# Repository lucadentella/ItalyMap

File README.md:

# ItalyMap

## Description / *Descrizione*
ItalyMap is an electronic project to create a dynamic map of Italy. Thanks to the use of RGB LEDs, one for each Italian region, it is possible to give a visual representation of data relating to these regions.

*ItalyMap è un progetto elettronico per realizzare una mappa dell'Italia dinamica. Grazie all'uso di led RGB, uno per ogni regione italiana, è possibile dare una rappresentazione visuale di dati relativi a tali regioni.*
## Folders / *Cartelle*
 - **eagle**, project in Autodesk Eagle format / *progetto in formato Autodesk Eagle*
 - **gerber**, gerber files ready for manufacturing (JLCPCB service) / *files gerber pronti per la produzione (service JLCPCB)*
 - **sketch**, Arduino programs (esp8266 board) / *programmi Arduino (scheda esp8266)*
 	 - Test_Italian-Flag, displays italian flag / *visualizza la bandiera italiana*
	 - Covid_NewCases-perRegion, displays the new Covid-19 cases / *visualizza i nuovi casi di Covid-19*
	 - Covid_VaccinationRate-perRegion, displays the vaccination rate / *visualizza il numero di vaccinazioni*
## Partlist / *Elenco componenti*
 - [SK6812 MINI-E](https://www.aliexpress.com/item/4000475685852.html) addressable LED
 - 1x03 pinhead
 - Wemos D1 Mini (to run Arduino example)
### Test_Italian-Flag:
 
### Covid_NewCases-perRegion:
 
### Covid_VaccinationRate-perRegion:

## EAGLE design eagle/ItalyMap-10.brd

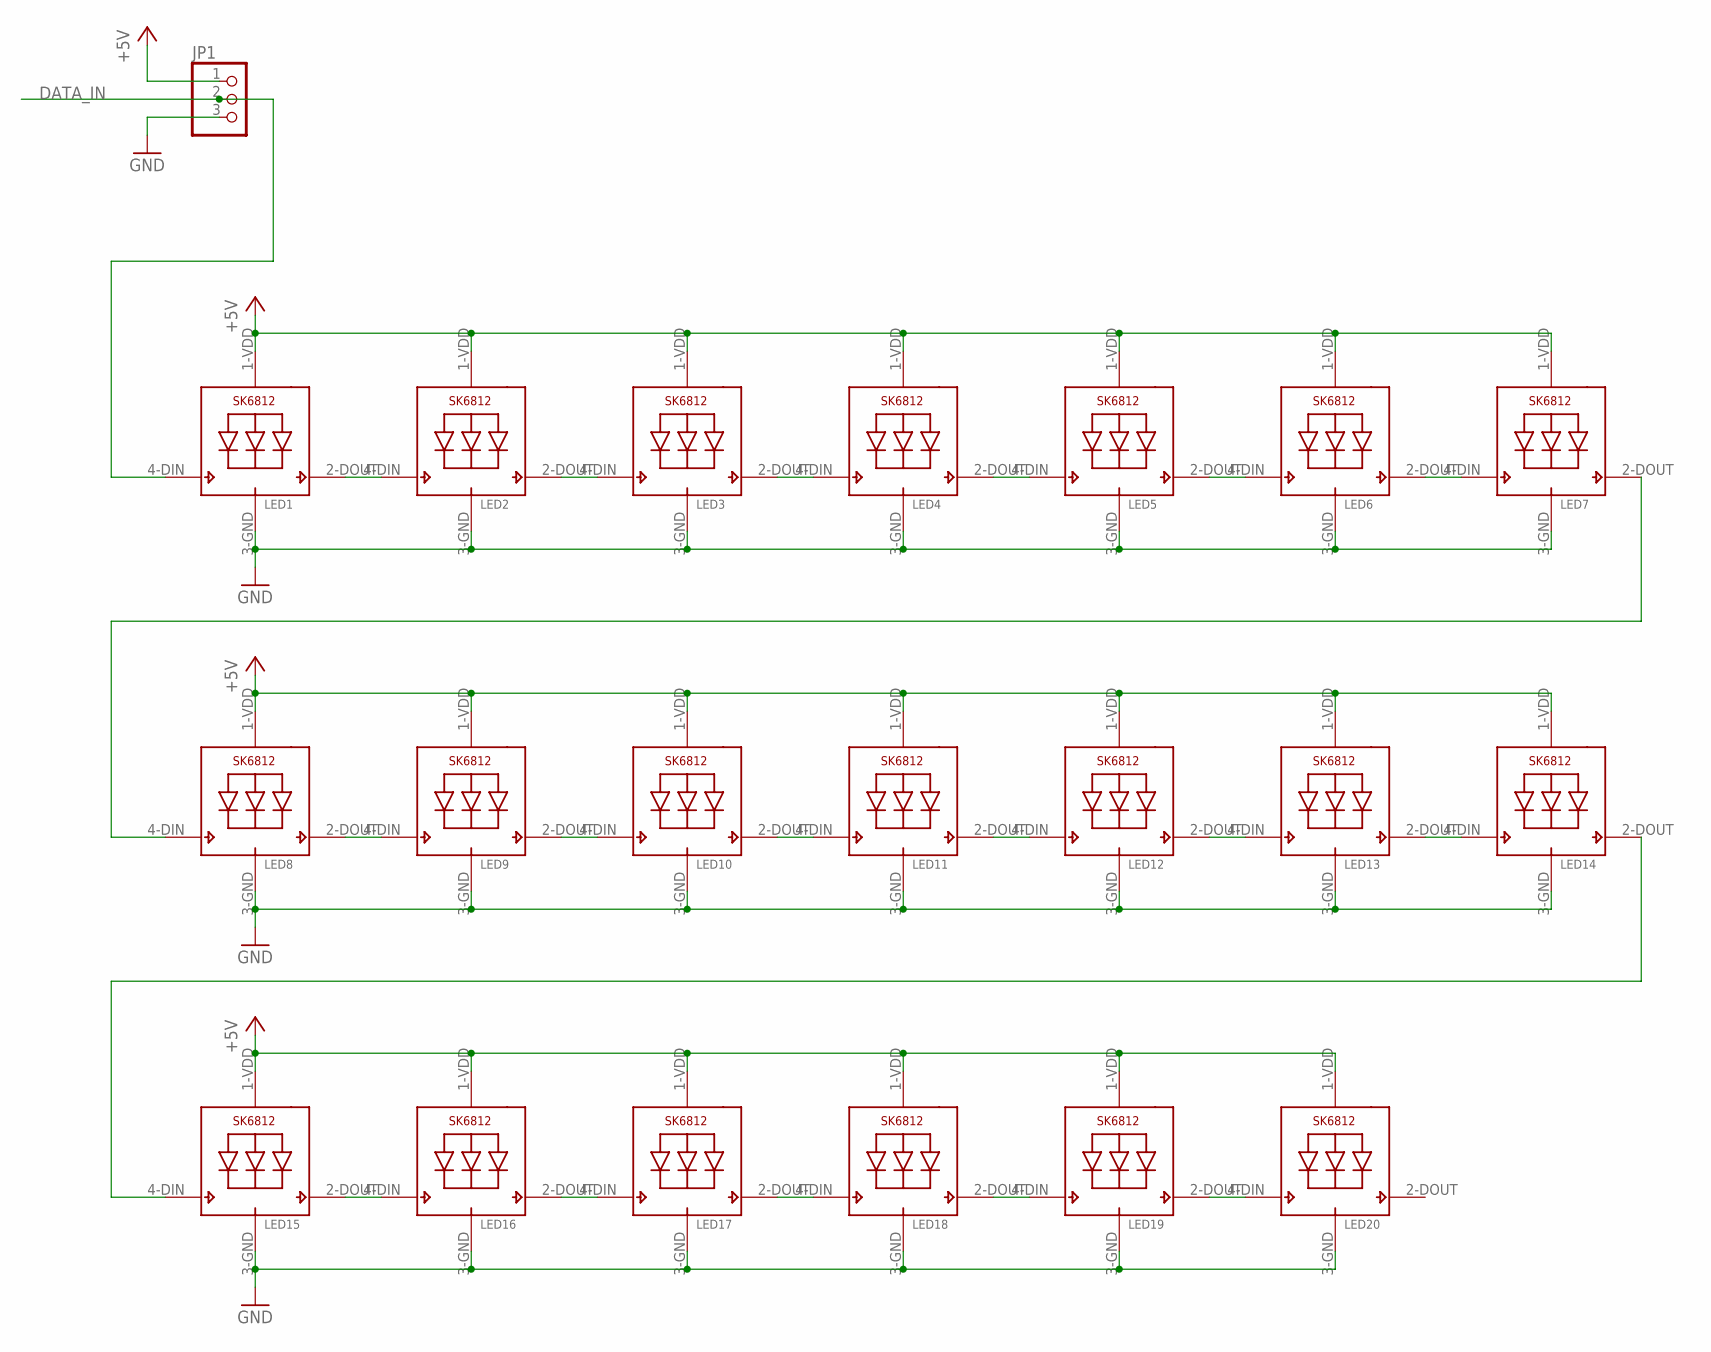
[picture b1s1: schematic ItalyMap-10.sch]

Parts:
JP1: PINHD-1X3; 1X03
LED1, LED2, LED3, LED4, LED5, LED6, LED7, LED8, LED9, LED10, LED11, LED12, LED13, LED14, LED15, LED16, LED17, LED18, LED19, LED20: SK6812; LED3228

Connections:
+5V: JP1.1, LED1.1-VDD (VDD), LED2.1-VDD (VDD), LED3.1-VDD (VDD), LED4.1-VDD (VDD), LED5.1-VDD (VDD), LED6.1-VDD (VDD), LED7.1-VDD (VDD), LED8.1-VDD (VDD), LED9.1-VDD (VDD), LED10.1-VDD (VDD), LED11.1-VDD (VDD), LED12.1-VDD (VDD), LED13.1-VDD (VDD), LED14.1-VDD (VDD), LED15.1-VDD (VDD), LED16.1-VDD (VDD), LED17.1-VDD (VDD), LED18.1-VDD (VDD), LED19.1-VDD (VDD), LED20.1-VDD (VDD)
DATA_IN: JP1.2, LED1.4-DIN (DI)
GND: JP1.3, LED1.3-GND (GND), LED2.3-GND (GND), LED3.3-GND (GND), LED4.3-GND (GND), LED5.3-GND (GND), LED6.3-GND (GND), LED7.3-GND (GND), LED8.3-GND (GND), LED9.3-GND (GND), LED10.3-GND (GND), LED11.3-GND (GND), LED12.3-GND (GND), LED13.3-GND (GND), LED14.3-GND (GND), LED15.3-GND (GND), LED16.3-GND (GND), LED17.3-GND (GND), LED18.3-GND (GND), LED19.3-GND (GND), LED20.3-GND (GND)
unnamed: LED7.2-DOUT (DO), LED8.4-DIN (DI)
unnamed: LED1.2-DOUT (DO), LED2.4-DIN (DI)
unnamed: LED2.2-DOUT (DO), LED3.4-DIN (DI)
unnamed: LED3.2-DOUT (DO), LED4.4-DIN (DI)
unnamed: LED4.2-DOUT (DO), LED5.4-DIN (DI)
unnamed: LED5.2-DOUT (DO), LED6.4-DIN (DI)
unnamed: LED6.2-DOUT (DO), LED7.4-DIN (DI)
unnamed: LED8.2-DOUT (DO), LED9.4-DIN (DI)
unnamed: LED9.2-DOUT (DO), LED10.4-DIN (DI)
unnamed: LED10.2-DOUT (DO), LED11.4-DIN (DI)
unnamed: LED11.2-DOUT (DO), LED12.4-DIN (DI)
unnamed: LED12.2-DOUT (DO), LED13.4-DIN (DI)
unnamed: LED13.2-DOUT (DO), LED14.4-DIN (DI)
unnamed: LED14.2-DOUT (DO), LED15.4-DIN (DI)
unnamed: LED15.2-DOUT (DO), LED16.4-DIN (DI)
unnamed: LED16.2-DOUT (DO), LED17.4-DIN (DI)
unnamed: LED17.2-DOUT (DO), LED18.4-DIN (DI)
unnamed: LED18.2-DOUT (DO), LED19.4-DIN (DI)
unnamed: LED19.2-DOUT (DO), LED20.4-DIN (DI)

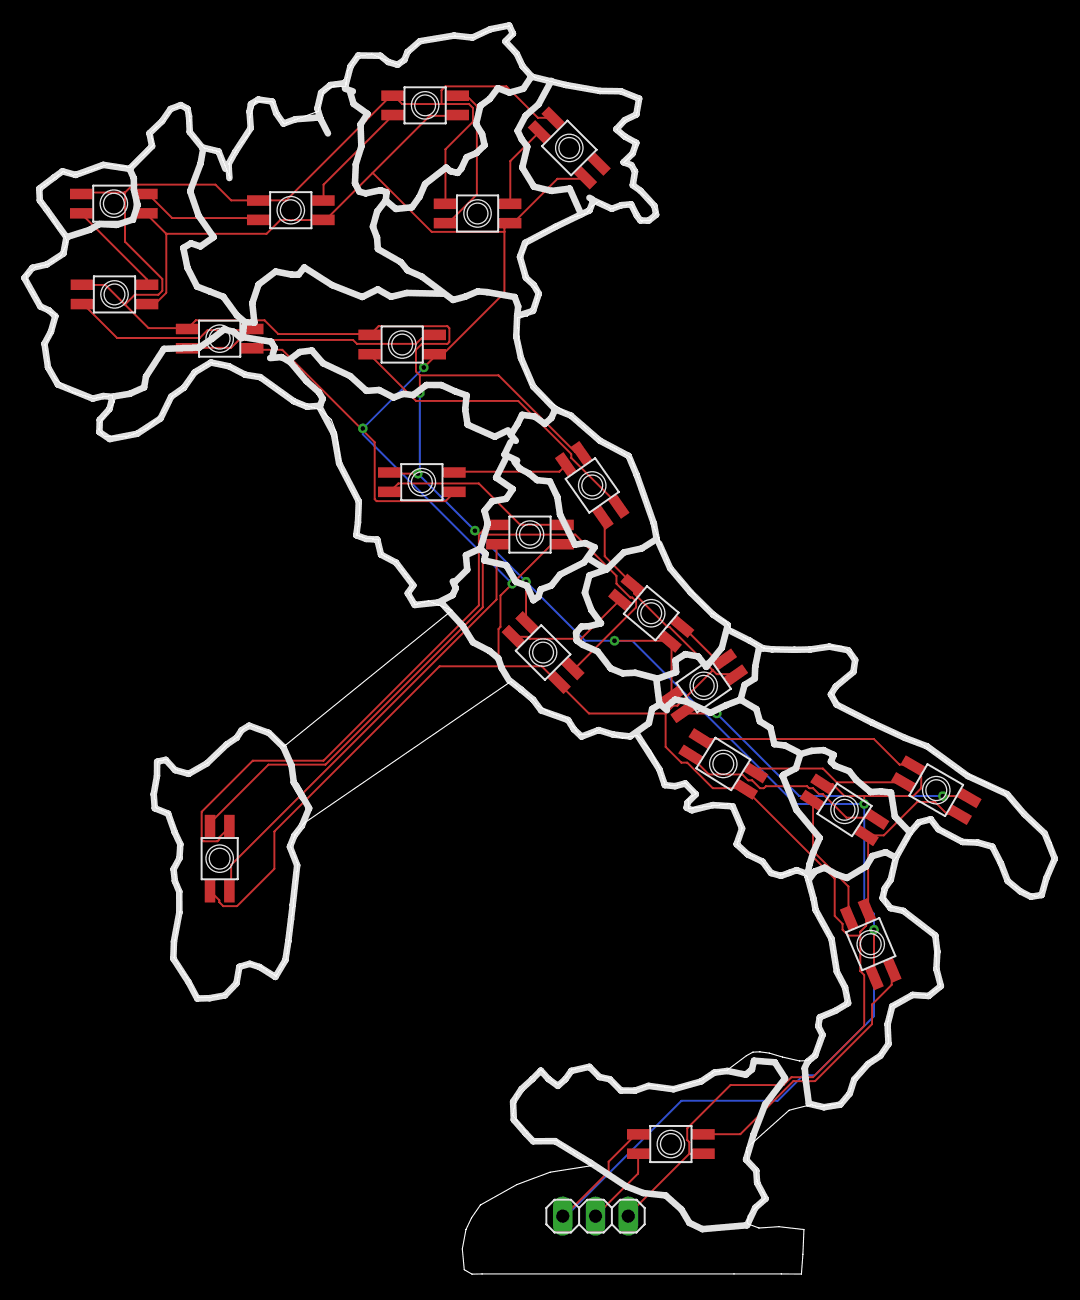
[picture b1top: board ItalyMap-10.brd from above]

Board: 2 copper layers, 79.7 x 96.8 mm, 21 parts (0 on the bottom side), 22 nets.

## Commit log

2021-01-05 README updated
2021-01-09 Arduino sketches
2021-01-09 Images added
2021-01-09 Eagle and gerber files added
2021-01-11 Vaccination Rate example added
2021-01-11 fix typo
2021-01-15 Add license (closes #1 )
